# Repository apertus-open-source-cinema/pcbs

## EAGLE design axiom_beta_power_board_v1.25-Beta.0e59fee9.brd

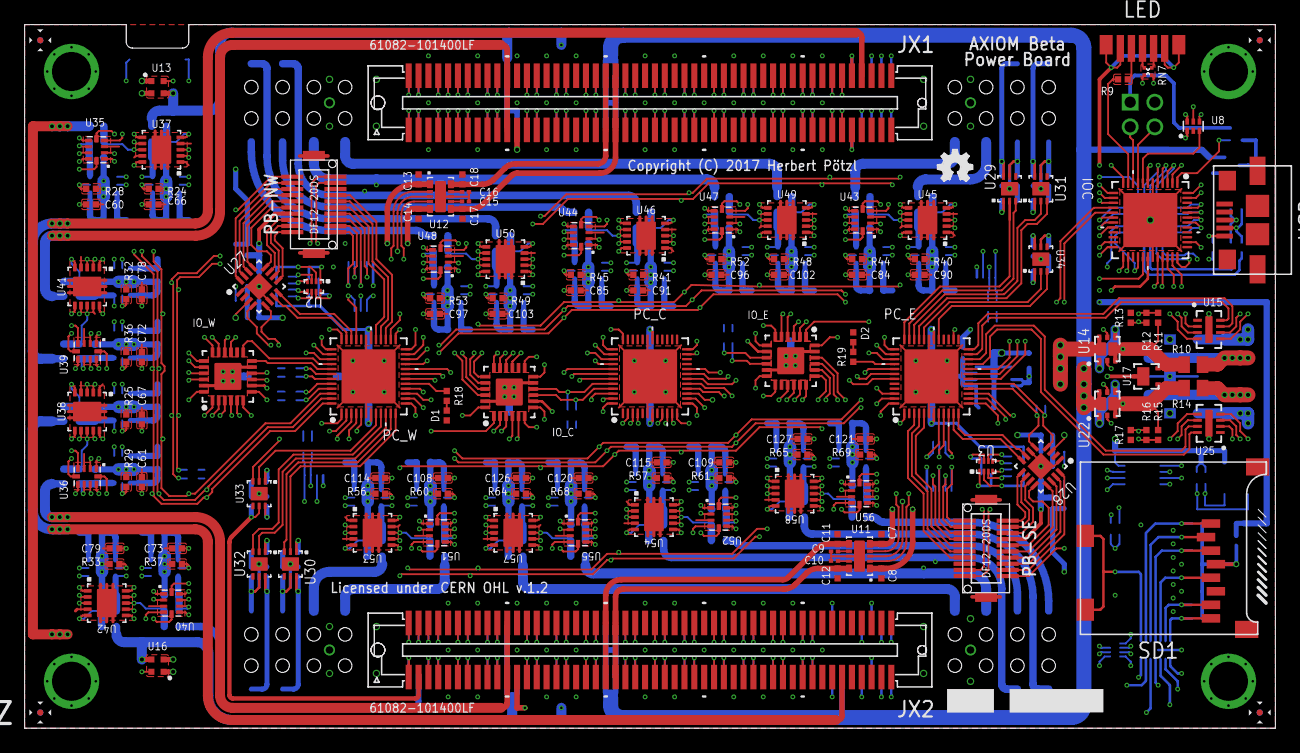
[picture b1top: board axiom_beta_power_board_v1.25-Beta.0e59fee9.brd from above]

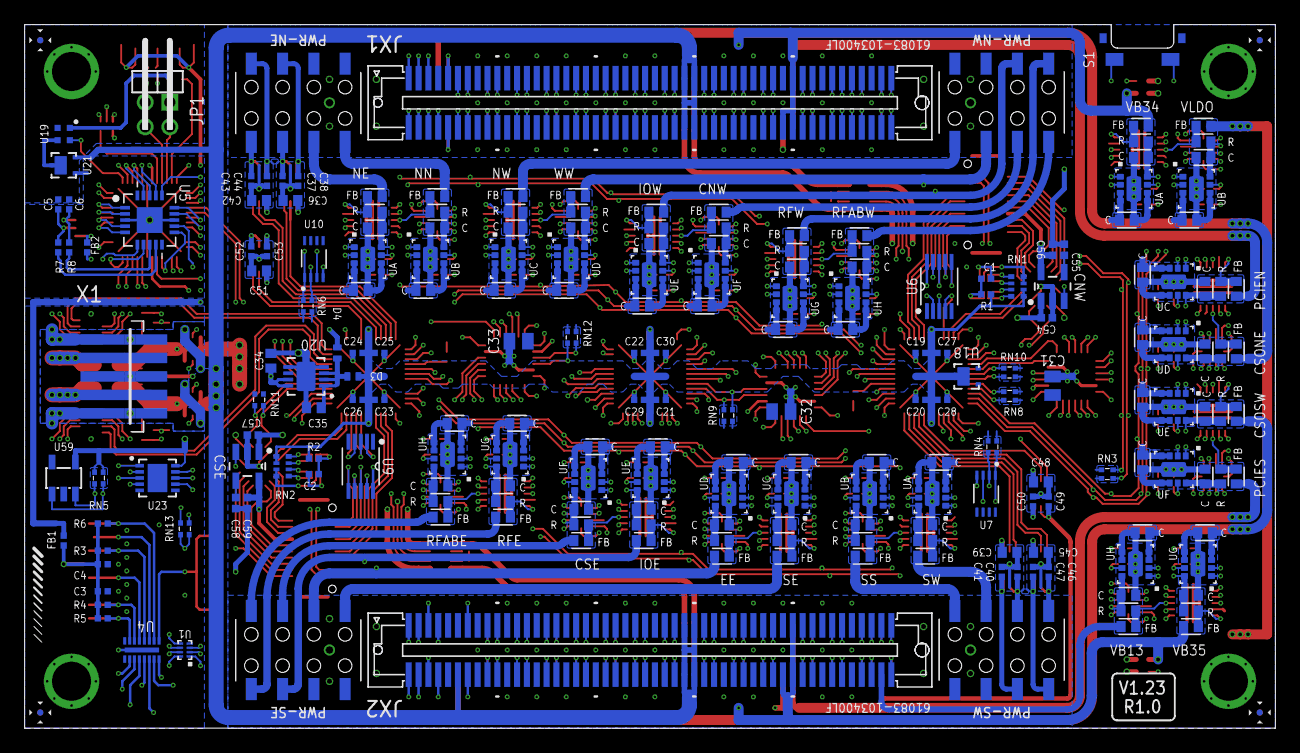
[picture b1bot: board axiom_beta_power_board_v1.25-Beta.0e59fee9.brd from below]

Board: 4 copper layers, 101.6 x 57.1 mm, 354 parts (218 on the bottom side), 496 nets.

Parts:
BETA: µZ-FCI-SOCKET-NOHOLES-R; µZ-SOCKET-NOHOLES-R
C1, C2: 10n; 0402-C
C3, C37, C38, C40, C41, C43, C44, C46, C47, C49, C50, C52, C53: 1u; 0402-C
C4, C19, C20, C21, C22, C23, C24: 100n; 0402-C
C5, C6, C7, C8, C11, C12, C13, C14, C17, C18, C60, C61, C66, C67, C72, C73, C78, C79, C84, C85, C90, C91, C96, C97, C102, C103, C108, C109, C114, C115, C120, C121, C126, C127: 0402-C
C9, C10, C15, C16: 0201-C
C25, C26, C27, C28, C29, C30: 4u7; 0402-C
C31, C32, C33: 47u; 0805-C
C34, C35: 10u; 0603-C
C36, C39, C42, C45, C48, C51: 4u7; 0603-C
C54, C56, C57, C59: 1u; 0402-B
C55, C58: 10n; 0402-B
C62, C63, C64, C65, C68, C69, C70, C71, C74, C75, C76, C77, C80, C81, C82, C83, C86, C87, C88, C89, C92, C93, C94, C95, C98, C99, C100, C101, C104, C105, C106, C107, C110, C111, C112, C113, C116, C117, C118, C119, C122, C123, C124, C125, C128, C129, C130, C131: 0603-C
CNW: SPX3819M5-L; SOT95P280X145-5N
CSE: SPX3819M5-L; SOT95P280X145-5N
D1, D2: 0402-C
D3, D4: PMEG2010BELD; DFN1006D-2
F1, F2, F3, F4, F5, F6, F7, F8: FIDUCIAL; FID_ARROW
FB1, FB2: 0402-C
FB3, FB4, FB5, FB6, FB7, FB8, FB9, FB10, FB11, FB12, FB13, FB14, FB15, FB16, FB17, FB18, FB19, FB20, FB21, FB22, FB23, FB24, FB25, FB26: 0603-C
IOC: PIC16F15386; UQFN40P600X600X100-49N-NSM
IO_C: MCP23018; QFN50P400X400X80-25N-NSM
IO_E: MCP23018; QFN50P400X400X80-25N-NSM
IO_W: MCP23018; QFN50P400X400X80-25N-NSM
JP1: 2X02M/90-S
LED: MSL0104RGB; MSL0104
LOGO2: OSHW_LOGO_FILLX0100-NT; OSHW_FILLX100_NOTEXT
PB-NW: DF12(XX)-20DP-0.5V
PB-SE: DF12(XX)-20DP-0.5V
PC_C: PIC16F15386; UQFN40P600X600X100-49N-NSM
PC_E: PIC16F15386; UQFN40P600X600X100-49N-NSM
PC_W: PIC16F15386; UQFN40P600X600X100-49N-NSM
PWR-NE: PINRC-2X04; R2X04
PWR-NW: PINRC-2X04; R2X04
PWR-SE: PINRC-2X04; R2X04
PWR-SW: PINRC-2X04; R2X04
R1, R2: 200k; 0402-C
R3, R4, R5, R6: 50k; 0402-C
R7, R8, R9, R11, R12, R13, R15, R16, R17, R18, R19, R24, R25, R28, R29, R32, R33, R36, R37, R40, R41, R44, R45, R48, R49, R52, R53, R56, R57, R60, R61, R64, R65, R68, R69: 0402-C
R10, R14: 0805-C
R22, R23, R26, R27, R30, R31, R34, R35, R38, R39, R42, R43, R46, R47, R50, R51, R54, R55, R58, R59, R62, R63, R66, R67: 0603-C
RN1, RN2: 4X0402ARV341
RN3, RN4, RN5, RN6, RN8, RN9, RN10, RN11, RN12, RN13: EXB24V
RN7: EXB14V
S1: SKSNLAE010
SD1: MICRO-SD-2CD; TF-MICRO-SD_PP2
U1: TXS0102; X2SON-8
U2, U3: PCA9306; UDFN-8
U4: IP4251CZ16-8-TTL; SON40P135X330X55-17N
U5: FT231; QFN65P400X400X100-21N
U6, U9: MCP4728-E/UN; SOP50P490X110-10N
U7, U10: LM75BGD; SOT996-2/3
U8: FXLH1T45; MICROPAK-6
U11, U12: AP22966; V-DFN3020-14
U13, U16, U19: MIC94040; MLF-4
U14, U22: NTLUD4C26N; UDFN6
U15, U25: LTC4365; DFN8
U17, U18, U21: PMEG2020CPAS; DFN2020D-3
U20: LT1965; DFN3X3_8LEAD
U23: PAC1720; DFN3X3_10LEAD
U27, U28: MCP23009; QFN50P300X300X80-17N
U29, U30, U31, U32, U33, U34: AP7312-3333W6-7; DFN2018-6
U35, U36, U39, U40, U43, U44, U47, U48, U51, U52, U55, U56: ADS1018; X2QFN-10
U37, U38, U41, U42, U45, U46, U49, U50, U53, U54, U57, U58: MCP46X2; DFN-10
U59: 24AA00OT; SOT23-5L
UA: TPS82085; MICROSIP
UB: TPS82085DD; MICROSIP-DD
UC: TPS82085; MICROSIP
UD: TPS82085DD; MICROSIP-DD
UE: TPS82085; MICROSIP
UF: TPS82085DD; MICROSIP-DD
UG: TPS82085; MICROSIP
UH: TPS82085DD; MICROSIP-DD
USB: 5_USB_3S; MICRO-AB-H-SMT
U_I: TPS82085; MICROSIP
U_J: TPS82085DD; MICROSIP-DD
U_K: TPS82085; MICROSIP
U_L: TPS82085DD; MICROSIP-DD
U_M: TPS82085; MICROSIP
U_N: TPS82085DD; MICROSIP-DD
U_O: TPS82085; MICROSIP
U_P: TPS82085DD; MICROSIP-DD
U_Q: TPS82085; MICROSIP
U_R: TPS82085DD; MICROSIP-DD
U_S: TPS82085; MICROSIP
U_T: TPS82085DD; MICROSIP-DD
U_U: TPS82085; MICROSIP
U_V: TPS82085DD; MICROSIP-DD
U_W: TPS82085; MICROSIP
U_X: TPS82085DD; MICROSIP-DD
X1: PICO-SPOX-5
ZED: µZ-FCI-CONONLY; µZ-CONONLY

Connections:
!ALERT: PC_E.46, U23.7
!CS0: PC_W.36, U35.2
!CS1: PC_W.37, U39.2
!CS2: PC_W.39, U36.2
!CS3: PC_W.38, U40.2
!CS4: PC_C.36, U43.2
!CS5: PC_C.37, U47.2
!CS6: PC_C.38, U44.2
!CS7: PC_C.39, U48.2
!CS8: PC_C.12, U51.2
!CS9: PC_C.13, U55.2
!CS10: PC_C.14, U52.2
!CS11: PC_C.15, U56.2
!RESET: IOC.28, U5.11
ANY_IN: C34.1, U17.3, U17.4, U20.7, U20.8
A_!RST: PB-NW.1, PC_W.25
A_SCL: PB-NW.2, RN1.1, U2.3
A_SDA: PB-NW.4, RN1.2, U2.4
BANK13_00_N: BETA.89, ZED.89
BANK13_00_P: BETA.87, ZED.87
BANK13_01_N: BETA.90, ZED.90
BANK13_01_P: BETA.88, ZED.88
BANK13_02_N: BETA.93, ZED.93
BANK13_02_P: BETA.91, ZED.91
BANK13_03_N: BETA.94, ZED.94
BANK13_03_P: BETA.92, ZED.92
BANK13_04_N: BETA.195, ZED.195
BANK13_04_P: BETA.193, ZED.193
BANK13_05_N: BETA.196, ZED.196
BANK13_05_P: BETA.194, ZED.194
BANK13_06_N: BETA.199, ZED.199
BANK13_06_P: BETA.197, ZED.197
BANK13_SE_0: BETA.200, ZED.200
BETA_5V: C7.1, C8.1, C13.1, C14.1, C31.1, C32.1, C33.1, C60.1, C61.1, C62.1, C64.1, C66.1, C67.1, C68.1, C70.1, C72.1, C73.1, C74.1, C76.1, C78.1, C79.1, C80.1, C82.1, C84.1, C85.1, C86.1, C88.1, C90.1, C91.1, C92.1, C94.1, C96.1, C97.1, C98.1, C100.1, C102.1, C103.1, C104.1, C106.1, C108.1, C109.1, C110.1, C112.1, C114.1, C115.1, C116.1, C118.1, C120.1, C121.1, C122.1, C124.1, C126.1, C127.1, C128.1, C130.1, IO_C.8, IO_E.8, IO_W.8, RN3.3, RN3.4, RN4.3, RN4.4, RN5.3, RN5.4, RN6.3, RN6.4, RN8.3, RN8.4, RN9.3, RN9.4, RN10.3, RN10.4, RN11.3, RN11.4, RN12.3, RN12.4, U6.1, U7.5, U7.6, U7.7, U7.8, U9.1, U10.5, U10.6, U10.7, U10.8, U11.1, U11.3, U11.5, U12.1, U12.3, U12.5, U14.6, U14.D1, U15.6, U18.1, U18.2, U23.10, U27.3, U28.3, U35.8, U36.8, U37.10, U38.9, U38.10, U39.8, U40.8, U41.1, U41.10, U42.1, U42.9, U42.10, U43.8, U44.8, U45.10, U46.9, U46.10, U47.8, U48.8, U49.1, U49.10, U50.1, U50.9, U50.10, U51.8, U52.8, U53.10, U54.9, U54.10, U55.8, U56.8, U57.1, U57.10, U58.1, U58.9, U58.10, U59.4, UA.3, UA.4, UB.3, UB.4, UC.3, UC.4, UD.3, UD.4, UE.3, UE.4, UF.3, UF.4, UG.3, UG.4, UH.3, UH.4, U_I.3, U_I.4, U_J.3, U_J.4, U_K.3, U_K.4, U_L.3, U_L.4, U_M.3, U_M.4, U_N.3, U_N.4, U_O.3, U_O.4, U_P.3, U_P.4, U_Q.3, U_Q.4, U_R.3, U_R.4, U_S.3, U_S.4, U_T.3, U_T.4, U_U.3, U_U.4, U_V.3, U_V.4, U_W.3, U_W.4, U_X.3, U_X.4
BETA_!FAULT: PC_E.24, U15.7
BETA_!SHDN: PC_E.23, U15.8
BETA_GATE: U14.2, U14.5, U15.5
BETA_IN: R10.2, R11.1, U14.3, U14.D2, U15.4, U17.2, U23.2
BETA_OV: R12.2, R13.1, U15.2
BETA_SUP: R10.1, U23.1, X1.4, X1.4A
BETA_UV: R11.2, R12.1, U15.3
BTN: PC_W.26, S1.2
B_!RST: PB-SE.1, PC_E.13
B_SCL: PB-SE.2, RN2.1, U3.3
B_SDA: PB-SE.4, RN2.2, U3.4
CBUS2: IOC.36, U5.7
CC_!MCLR: IOC.20, U5.16
CC_JX1: IOC.8, U8.3
CC_PCLK: IOC.18, U5.15
CC_PDAT: IOC.19, U5.14
CC_SE_0: IOC.47, U1.6
CC_SE_1: IOC.48, U1.7
CD: SD1.CD1, SD1.CD2, U4.1
CD': IOC.32, U4.16
CLK: SD1.5, U4.5
CMD: R3.2, SD1.3, U4.4
CNW_EN: CNW.3, PC_W.22
CNW_PG: C55.1, CNW.4
CSE_EN: CSE.3, PC_E.15
CSE_PG: C58.1, CSE.4
CSO_NE_V: BETA.7, FB9.2
CSO_NW_V: FB14.2, PWR-NW.6
CSO_SE_V: FB22.2, PWR-SE.6
CSO_SW_V: BETA.112, FB4.2
D0: IOC.5, U5.17
D1: IOC.45, U5.1
D2: IOC.3, U5.19
D3: IOC.2, U5.6
D4: IOC.4, U5.18
D5: IOC.43, U5.4
D6: IOC.42, U5.5
D7: IOC.44, U5.2
DAT0: R4.2, SD1.7, U4.6
DAT1: R5.2, SD1.8, U4.7
DAT2: R6.2, SD1.1, U4.2
DAT3: SD1.2, U4.3
DM: R7.2, U5.9
DP: R8.2, U5.8
DXP_0_N: BETA.100, ZED.100
DXP_0_P: BETA.98, ZED.98
EN_A: IO_W.16, UA.1
EN_B: IO_W.18, UB.1
EN_C: IO_W.20, UC.1
EN_D: IO_W.22, UD.1
EN_E: IO_W.1, UE.1
EN_F: IO_W.3, UF.1
EN_G: IO_W.5, UG.1
EN_H: IO_W.7, UH.1
EN_I: IO_E.1, U_I.1
EN_J: IO_E.3, U_J.1
EN_K: IO_E.5, U_K.1
EN_L: IO_E.7, U_L.1
EN_M: IO_C.16, U_M.1
EN_N: IO_C.18, U_N.1
EN_O: IO_C.20, U_O.1
EN_P: IO_C.22, U_P.1
EN_Q: IO_C.1, U_Q.1
EN_R: IO_C.3, U_R.1
EN_S: IO_C.5, U_S.1
EN_T: IO_C.7, U_T.1
EN_U: IO_E.16, U_U.1
EN_V: IO_E.18, U_V.1
EN_W: IO_E.20, U_W.1
EN_X: IO_E.22, U_X.1
EXTA: IOC.10, JP1.2
EXTB: IOC.9, JP1.4
E_B_SCL: PC_E.47, RN2.4, U3.6
E_B_SDA: PC_E.48, RN2.3, U3.5
E_I2C_EN: PC_E.36, U29.2
E_I2C_V: C38.1, PWR-NE.6, U29.6
E_RC2: PC_E.40, R19.1
E_SPI_EN: PC_E.34, U31.2
E_SPI_V: C44.1, PWR-NE.8, U31.6
E_VE: FB25.2, PC_E.1, PWR-SE.4
E_VE_CV: PB-SE.20, U9.6
E_VE_OV: PB-SE.9, U28.13
E_VE_UV: PB-SE.11, U28.12
FAN_SUP: JP1.1, U19.1
FAN_SUP_EN: IOC.1, U19.4
FB_A: R24.2, U37.6, UA.7
FB_B: R28.2, U37.7, UB.7
FB_C: R32.2, U41.6, UC.7
FB_D: R36.2, U41.7, UD.7
FB_E: R25.2, U38.6, UE.7
FB_F: R29.2, U38.7, UF.7
FB_G: R33.2, U42.6, UG.7
FB_H: R37.2, U42.7, UH.7
FB_I: R40.2, U45.6, U_I.7
FB_J: R44.2, U45.7, U_J.7
FB_K: R48.2, U49.6, U_K.7
FB_L: R52.2, U49.7, U_L.7
FB_M: R41.2, U46.6, U_M.7
FB_N: R45.2, U46.7, U_N.7
FB_O: R49.2, U50.6, U_O.7
FB_P: R53.2, U50.7, U_P.7
FB_Q: R56.2, U53.6, U_Q.7
FB_R: R60.2, U53.7, U_R.7
FB_S: R64.2, U57.6, U_S.7
FB_T: R68.2, U57.7, U_T.7
FB_U: R57.2, U54.6, U_U.7
FB_V: R61.2, U54.7, U_V.7
FB_W: R65.2, U58.6, U_W.7
FB_X: R69.2, U58.7, U_X.7
GND: BETA.15, BETA.16, BETA.21, BETA.22, BETA.27, BETA.28, BETA.33, BETA.34, BETA.39, BETA.40, BETA.45, BETA.46, BETA.51, BETA.52, BETA.65, BETA.66, BETA.71, BETA.72, BETA.77, BETA.85, BETA.86, BETA.95, BETA.96, BETA.115, BETA.116, BETA.121, BETA.122, BETA.127, BETA.128, BETA.133, BETA.134, BETA.139, BETA.140, BETA.145, BETA.146, BETA.151, BETA.152, BETA.165, BETA.166, BETA.171, BETA.172, BETA.177, BETA.185, BETA.186, BETA.191, BETA.192, C1.2, C2.2, C3.2, C4.2, C5.2, C6.2, C7.2, C8.2, C9.2, C10.2, C11.2, C12.2, C13.2, C14.2, C15.2, C16.2, C17.2, C18.2, C19.2, C20.2, C21.2, C22.2, C23.2, C24.2, C25.2, C26.2, C27.2, C28.2, C29.2, C30.2, C31.2, C32.2, C33.2, C34.2, C35.2, C36.2, C37.2, C38.2, C39.2, C40.2, C41.2, C42.2, C43.2, C44.2, C45.2, C46.2, C47.2, C48.2, C49.2, C50.2, C51.2, C52.2, C53.2, C54.2, C55.2, C56.2, C57.2, C58.2, C59.2, C60.2, C61.2, C62.2, C63.2, C64.2, C65.2, C66.2, C67.2, C68.2, C69.2, C70.2, C71.2, C72.2, C73.2, C74.2, C75.2, C76.2, C77.2, C78.2, C79.2, C80.2, C81.2, C82.2, C83.2, C84.2, C85.2, C86.2, C87.2, C88.2, C89.2, C90.2, C91.2, C92.2, C93.2, C94.2, C95.2, C96.2, C97.2, C98.2, C99.2, C100.2, C101.2, C102.2, C103.2, C104.2, C105.2, C106.2, C107.2, C108.2, C109.2, C110.2, C111.2, C112.2, C113.2, C114.2, C115.2, C116.2, C117.2, C118.2, C119.2, C120.2, C121.2, C122.2, C123.2, C124.2, C125.2, C126.2, C127.2, C128.2, C129.2, C130.2, C131.2, CNW.2, CSE.2, D1.2, D2.2, IOC.6, IOC.31, IOC.EP, IO_C.11, IO_C.23, IO_C.25, IO_E.11, IO_E.23, IO_E.25, IO_W.11, IO_W.23, IO_W.25, JP1.3, PB-NW.6, PB-SE.6, PC_C.6, PC_C.31, PC_C.EP, PC_E.6, PC_E.31, PC_E.EP, PC_W.6, PC_W.31, PC_W.EP, PWR-NE.2, PWR-NE.4, PWR-NW.1, PWR-NW.3, PWR-SE.1, PWR-SE.3, PWR-SW.2, PWR-SW.4, R13.2, R17.2, R24.1, R25.1, R28.1, R29.1, R32.1, R33.1, R36.1, R37.1, R40.1, R41.1, R44.1, R45.1, R48.1, R49.1, R52.1, R53.1, R56.1, R57.1, R60.1, R61.1, R64.1, R65.1, R68.1, R69.1, S1.1, SD1.6, SD1.MT1, SD1.MT2, U1.4, U2.1, U3.1, U4.17, U5.3, U5.13, U5.EP, U6.10, U7.4, U8.2, U9.10, U10.4, U11.8, U11.EP, U12.8, U12.EP, U13.2, U15.1, U15.EP, U16.2, U19.2, U20.4, U20.5, U20.9, U23.5, U23.6, U23.EPAD, U25.1, U25.EP, U27.1, U27.6, U27.EP, U28.1, U28.6, U28.EP, U29.4, U29.10, U30.4, U30.10, U31.4, U31.10, U32.4, U32.10, U33.4, U33.10, U34.4, U34.10, U35.3, U36.3, U37.1, U37.4, U37.9, U37.EP, U38.1, U38.4, U38.EP, U39.3, U40.3, U41.4, U41.9, U41.EP, U42.4, U42.EP, U43.3, U44.3, U45.1, U45.4, U45.9, U45.EP, U46.1, U46.4, U46.EP, U47.3, U48.3, U49.4, U49.9, U49.EP, U50.4, U50.EP, U51.3, U52.3, U53.1, U53.4, U53.9, U53.EP, U54.1, U54.4, U54.EP, U55.3, U56.3, U57.4, U57.9, U57.EP, U58.4, U58.EP, U59.2, UA.5, UA.6, UA.EP, UB.5, UB.6, UB.EP, UC.5, UC.6, UC.EP, UD.5, UD.6, UD.EP, UE.5, UE.6, UE.EP, UF.5, UF.6, UF.EP, UG.5, UG.6, UG.EP, UH.5, UH.6, UH.EP, USB.5, U_I.5, U_I.6, U_I.EP, U_J.5, U_J.6, U_J.EP, U_K.5, U_K.6, U_K.EP, U_L.5, U_L.6, U_L.EP, U_M.5, U_M.6, U_M.EP, U_N.5, U_N.6, U_N.EP, U_O.5, U_O.6, U_O.EP, U_P.5, U_P.6, U_P.EP, U_Q.5, U_Q.6, U_Q.EP, U_R.5, U_R.6, U_R.EP, U_S.5, U_S.6, U_S.EP, U_T.5, U_T.6, U_T.EP, U_U.5, U_U.6, U_U.EP, U_V.5, U_V.6, U_V.EP, U_W.5, U_W.6, U_W.EP, U_X.5, U_X.6, U_X.EP, X1.1, X1.1A, X1.5, X1.5A, ZED.15, ZED.16, ZED.21, ZED.22, ZED.27, ZED.28, ZED.33, ZED.34, ZED.39, ZED.40, ZED.45, ZED.46, ZED.51, ZED.52, ZED.65, ZED.66, ZED.71, ZED.72, ZED.77, ZED.85, ZED.86, ZED.95, ZED.96, ZED.115, ZED.116, ZED.121, ZED.122, ZED.127, ZED.128, ZED.133, ZED.134, ZED.139, ZED.140, ZED.145, ZED.146, ZED.151, ZED.152, ZED.165, ZED.166, ZED.171, ZED.172, ZED.177, ZED.185, ZED.186, ZED.191, ZED.192
IOC_!RST: IO_C.12, PC_C.46
IOC_INT: IO_C.13, PC_C.40
IOC_SCL: IO_C.9, PC_C.45, RN9.2
IOC_SDA: IO_C.10, PC_C.44, RN9.1
IOE_!RST: IO_E.12, PC_C.23
IOE_INT: IO_E.13, PC_C.24
IOE_SCL: IO_E.9, RN12.2
IOE_SDA: IO_E.10, RN12.1
IOE_V: FB20.2, PWR-SE.5, RN2.7, RN2.8, U3.2
IONW_SCL: PC_W.43, RN10.2, U27.4
IONW_SDA: PC_W.42, RN10.1, U27.5
IOSE_SCL: PC_E.17, RN11.1, U28.4
IOSE_SDA: PC_E.16, RN11.2, U28.5
IOW_!RST: IO_W.12, PC_W.41
IOW_INT: IO_W.13, PC_W.40
IOW_SCL: IO_W.9, PC_W.45, RN8.2
IOW_SDA: IO_W.10, PC_W.44, RN8.1
IOW_V: FB12.2, PWR-NW.5, RN1.7, RN1.8, U2.2
JTAG_EN: PC_W.10, U32.2
JTAG_V: C47.1, PWR-SW.8, U32.6
JX1_00_N: BETA.13, ZED.13
JX1_00_P: BETA.11, ZED.11
JX1_01_N: BETA.14, ZED.14
JX1_01_P: BETA.12, ZED.12
JX1_02_N: BETA.19, ZED.19
JX1_02_P: BETA.17, ZED.17
JX1_03_N: BETA.20, ZED.20
JX1_03_P: BETA.18, ZED.18
JX1_04_N: BETA.25, ZED.25
JX1_04_P: BETA.23, ZED.23
JX1_05_N: BETA.26, ZED.26
JX1_05_P: BETA.24, ZED.24
JX1_06_N: BETA.31, ZED.31
JX1_06_P: BETA.29, ZED.29
JX1_07_N: BETA.32, ZED.32
JX1_07_P: BETA.30, ZED.30
JX1_08_N: BETA.37, ZED.37
JX1_08_P: BETA.35, ZED.35
JX1_09_N: BETA.38, ZED.38
JX1_09_P: BETA.36, ZED.36
JX1_10_N: BETA.43, ZED.43
JX1_10_P: BETA.41, ZED.41
JX1_11_N: BETA.44, ZED.44
JX1_11_P: BETA.42, ZED.42
JX1_12_N: BETA.49, ZED.49
JX1_12_P: BETA.47, ZED.47
JX1_13_N: BETA.50, ZED.50
JX1_13_P: BETA.48, ZED.48
JX1_14_N: BETA.55, ZED.55
JX1_14_P: BETA.53, ZED.53
JX1_15_N: BETA.56, ZED.56
JX1_15_P: BETA.54, ZED.54
JX1_16_N: BETA.63, ZED.63
JX1_16_P: BETA.61, ZED.61
JX1_17_N: BETA.64, ZED.64
JX1_17_P: BETA.62, ZED.62
JX1_18_N: BETA.69, ZED.69
JX1_18_P: BETA.67, ZED.67
JX1_19_N: BETA.70, ZED.70
JX1_19_P: BETA.68, ZED.68
JX1_20_N: BETA.75, ZED.75
JX1_20_P: BETA.73, ZED.73
JX1_21_N: BETA.76, ZED.76
JX1_21_P: BETA.74, ZED.74
JX1_22_N: BETA.83, ZED.83
JX1_22_P: BETA.81, ZED.81
JX1_23_N: BETA.84, ZED.84
JX1_23_P: BETA.82, ZED.82
JX1_DIR: IOC.38, U8.5
JX1_SE_0: BETA.9, ZED.9
JX1_SE_1: BETA.10, U8.4, ZED.10
JX2_00_N: BETA.119, ZED.119
JX2_00_P: BETA.117, ZED.117
JX2_01_N: BETA.120, ZED.120
JX2_01_P: BETA.118, ZED.118
JX2_02_N: BETA.125, ZED.125
JX2_02_P: BETA.123, ZED.123
JX2_03_N: BETA.126, ZED.126
JX2_03_P: BETA.124, ZED.124
JX2_04_N: BETA.131, ZED.131
JX2_04_P: BETA.129, ZED.129
JX2_05_N: BETA.132, ZED.132
JX2_05_P: BETA.130, ZED.130
JX2_06_N: BETA.137, ZED.137
JX2_06_P: BETA.135, ZED.135
JX2_07_N: BETA.138, ZED.138
JX2_07_P: BETA.136, ZED.136
JX2_08_N: BETA.143, ZED.143
JX2_08_P: BETA.141, ZED.141
JX2_09_N: BETA.144, ZED.144
JX2_09_P: BETA.142, ZED.142
JX2_10_N: BETA.149, ZED.149
JX2_10_P: BETA.147, ZED.147
JX2_11_N: BETA.150, ZED.150
JX2_11_P: BETA.148, ZED.148
JX2_12_N: BETA.155, ZED.155
JX2_12_P: BETA.153, ZED.153
JX2_13_N: BETA.156, ZED.156
JX2_13_P: BETA.154, ZED.154
JX2_14_N: BETA.163, ZED.163
JX2_14_P: BETA.161, ZED.161
JX2_15_N: BETA.164, ZED.164
JX2_15_P: BETA.162, ZED.162
JX2_16_N: BETA.169, ZED.169
JX2_16_P: BETA.167, ZED.167
JX2_17_N: BETA.170, ZED.170
JX2_17_P: BETA.168, ZED.168
JX2_18_N: BETA.175, ZED.175
JX2_18_P: BETA.173, ZED.173
JX2_19_N: BETA.176, ZED.176
JX2_19_P: BETA.174, ZED.174
JX2_20_N: BETA.183, ZED.183
JX2_20_P: BETA.181, ZED.181
JX2_21_N: BETA.184, ZED.184
JX2_21_P: BETA.182, ZED.182
JX2_22_N: BETA.189, ZED.189
JX2_22_P: BETA.187, ZED.187
JX2_23_N: BETA.190, ZED.190
JX2_23_P: BETA.188, ZED.188
JX2_SE_0: U1.3, ZED.113
JX2_SE_1: U1.2, ZED.114
LED_B: IOC.25, RN7.2
LED_G: IOC.11, R9.2
LED_R: IOC.26, RN7.1
MEAS_A: FB3.1, R22.2, U35.4, U37.5
MEAS_B: FB5.1, R26.2, U35.6, U37.8
MEAS_C: FB7.1, R30.2, U39.4, U41.5
MEAS_D: FB9.1, R34.2, U39.6, U41.8
MEAS_E: FB4.1, R23.2, U36.4, U38.5
MEAS_F: FB6.1, R27.2, U36.6, U38.8
MEAS_G: FB8.1, R31.2, U40.4, U42.5
MEAS_H: FB10.1, R35.2, U40.6, U42.8
MEAS_I: FB11.1, R38.2, U43.4, U45.5
MEAS_J: FB13.1, R42.2, U43.6, U45.8
MEAS_K: FB15.1, R46.2, U47.4, U49.5
MEAS_L: FB17.1, R50.2, U47.6, U49.8
MEAS_M: FB12.1, R39.2, U44.4, U46.5
MEAS_N: FB14.1, R43.2, U44.6, U46.8
MEAS_O: FB16.1, R47.2, U48.4, U50.5
MEAS_P: FB18.1, R51.2, U48.6, U50.8
MEAS_Q: FB19.1, R54.2, U51.4, U53.5
MEAS_R: FB21.1, R58.2, U51.6, U53.8
MEAS_S: FB23.1, R62.2, U55.4, U57.5
MEAS_T: FB25.1, R66.2, U55.6, U57.8
MEAS_U: FB20.1, R55.2, U52.4, U54.5
MEAS_V: FB22.1, R59.2, U52.6, U54.8
MEAS_W: FB24.1, R63.2, U56.4, U58.5
MEAS_X: FB26.1, R67.2, U56.6, U58.8
MIX_SUP: U19.3, U21.3, U21.4
unnamed: C3.1, C4.1, FB1.2, R3.1, R4.1, R5.1, R6.1, SD1.4
unnamed: LED.5, RN7.3
unnamed: LED.4, RN7.4
unnamed: LED.3, R9.1
unnamed: C5.1, R7.1, USB.2
unnamed: C6.1, R8.1, USB.3
unnamed: U14.1, U14.4
unnamed: C15.1, U12.7
unnamed: C16.1, U12.9
unnamed: C9.1, U11.7
unnamed: C10.1, U11.9
unnamed: D1.1, R18.2
unnamed: D2.1, R19.2
unnamed: C1.1, R1.2, U2.7, U2.8
unnamed: C2.1, R2.2, U3.7, U3.8
unnamed: U22.1, U22.4
NW_!LDAC: PC_W.33, U6.4
NW_!RST: PC_W.35, U27.7
NW_INT: PC_W.34, U27.8
N_CHK_V: C56.1, CNW.5, PB-NW.13, PC_W.23
N_I2C_EN: PC_E.33, U31.3
N_I2C_V: C43.1, PWR-NE.7, U31.5
N_SPI_EN: PC_E.35, U29.3
N_SPI_V: C37.1, PWR-NE.5, U29.5
N_VE: FB11.2, PWR-NE.3
N_VE_CV: PB-NW.18, U6.7
N_VE_OV: PB-NW.7, U27.14
N_VE_RS: PB-NW.8, PC_W.27
N_VE_UV: PB-NW.19, U27.9
N_VN: FB13.2, PWR-NE.1
N_VN_CV: PB-NW.16, U6.8
N_VN_OV: PB-NW.5, U27.15
N_VN_RS: PB-NW.12, PC_W.29
N_VN_UV: PB-NW.17, U27.10
N_VW: FB15.2, PWR-NW.2
N_VW_CV: PB-NW.14, U6.9
N_VW_OV: PB-NW.3, U27.16
N_VW_RS: PB-NW.10, PC_W.28
N_VW_UV: PB-NW.15, U27.11
OS2: PC_E.26, U10.3
OS3: PC_W.13, U7.3
PCC_!MCLR: PC_C.20, PC_E.41
PCC_PCLK: PC_C.18, PC_E.43
PCC_PDAT: PC_C.19, PC_E.42
PCE_!MCLR: IOC.29, PC_E.20
PCE_PCLK: IOC.17, PC_E.18
PCE_PDAT: IOC.16, PC_E.19
PCIE_I2C_EN: PC_W.1, U33.3
PCIE_I2C_V: BETA.198, C49.1, U33.5
PCIE_NIO_EN: PC_W.21, U13.4
PCIE_N_5V: BETA.59, BETA.60, C18.1, U12.10
PCIE_N_V: BETA.79, BETA.80, FB7.2
PCIE_N_VCCIO: BETA.78, U13.1
PCIE_SIO_EN: PC_W.14, U16.4
PCIE_S_5V: BETA.159, BETA.160, C11.1, U11.6
PCIE_S_V: BETA.179, BETA.180, FB6.2
PCIE_S_VCCIO: BETA.178, U16.1
PCW_!MCLR: PC_C.41, PC_W.20
PCW_PCLK: PC_C.43, PC_W.18
PCW_PDAT: PC_C.42, PC_W.19
PEX_N_V: BETA.57, BETA.58, C17.1, U12.6
PEX_S_V: BETA.157, BETA.158, C12.1, U11.10
PG_A: IO_W.15, UA.2
PG_B: IO_W.17, UB.2
PG_C: IO_W.19, UC.2
PG_D: IO_W.21, UD.2
PG_E: IO_W.24, UE.2
PG_F: IO_W.2, UF.2
PG_G: IO_W.4, UG.2
PG_H: IO_W.6, UH.2
PG_I: IO_E.24, U_I.2
PG_J: IO_E.2, U_J.2
PG_K: IO_E.4, U_K.2
PG_L: IO_E.6, U_L.2
PG_M: IO_C.15, U_M.2
PG_N: IO_C.17, U_N.2
PG_O: IO_C.19, U_O.2
PG_P: IO_C.21, U_P.2
PG_Q: IO_C.24, U_Q.2
PG_R: IO_C.2, U_R.2
PG_S: IO_C.4, U_S.2
PG_T: IO_C.6, U_T.2
PG_U: IO_E.15, U_U.2
PG_V: IO_E.17, U_V.2
PG_W: IO_E.19, U_W.2
PG_X: IO_E.21, U_X.2
PMOD_D0: U4.10, ZED.101
PMOD_D1: U4.11, ZED.102
PMOD_D2: U4.13, ZED.103
PMOD_D3: U4.12, ZED.104
PMOD_D6: U4.15, ZED.107
PMOD_D7: U4.14, ZED.108
PMOD_SCL: IOC.34, RN13.2, ZED.105
PMOD_SDA: IOC.35, RN13.1, ZED.106
RFAB_E_V: FB26.2, PWR-SE.8
RFAB_W_V: FB18.2, PWR-NW.8
RFE_V: FB24.2, PWR-SE.7
RFW_V: FB16.2, PWR-NW.7
SCK1: PC_W.46, U35.1, U36.1, U39.1, U40.1
SCK2: PC_C.9, U43.1, U44.1, U47.1, U48.1
SCK3: PC_C.4, U51.1, U52.1, U55.1, U56.1
SCL1: PC_W.5, RN3.2, U6.2, U37.2, U38.2, U41.2, U42.2
SCL2: PC_C.16, RN6.1, U10.2, U45.2, U46.2, U49.2, U50.2
SCL3: PC_C.48, RN4.1, U7.2, U53.2, U54.2, U57.2, U58.2
SCL4: PC_E.8, RN5.2, U9.2, U23.9, U59.1
SDA1: PC_W.4, RN3.1, U6.3, U37.3, U38.3, U41.3, U42.3
SDA2: PC_C.17, RN6.2, U10.1, U45.3, U46.3, U49.3, U50.3
SDA3: PC_C.47, RN4.2, U7.1, U53.3, U54.3, U57.3, U58.3
SDA4: PC_E.9, RN5.1, U9.3, U23.8, U59.3
SDI1: PC_W.48, U35.10, U36.10, U39.10, U40.10
SDI2: PC_C.10, U43.10, U44.10, U47.10, U48.10
SDI3: PC_C.3, U51.10, U52.10, U55.10, U56.10
SDO1: PC_W.47, U35.9, U36.9, U39.9, U40.9
SDO2: PC_C.11, U43.9, U44.9, U47.9, U48.9
SDO3: PC_C.2, U51.9, U52.9, U55.9, U56.9
SD_V: C52.1, FB1.1, U34.5
SD_V_EN: PC_E.29, U34.3
SENSE: X1.3, X1.3A
SE_!LDAC: PC_E.10, U9.4
SE_!RST: PC_E.12, U28.7
SE_INT: PC_E.11, U28.8
S_CHK_V: C59.1, CSE.5, PB-SE.13, PC_E.14
S_I2C_EN: PC_W.9, U32.3
S_I2C_V: C46.1, PWR-SW.7, U32.5
S_SPI_EN: PC_W.11, U30.3
S_SPI_V: C40.1, PWR-SW.5, U30.5
S_VE: FB23.2, PWR-SE.2
S_VE_CV: PB-SE.14, U9.9
S_VE_OV: PB-SE.3, U28.16
S_VE_RS: PB-SE.10, PC_E.4
S_VE_UV: PB-SE.15, U28.11
S_VS: FB21.2, PWR-SW.1
S_VS_CV: PB-SE.16, U9.8
S_VS_OV: PB-SE.5, U28.15
S_VS_RS: PB-SE.12, PC_E.5
S_VS_UV: PB-SE.17, U28.10
S_VW: FB19.2, PWR-SW.3
S_VW_CV: PB-SE.18, U9.7
S_VW_OV: PB-SE.7, U28.14
S_VW_RS: PB-SE.8, PC_E.3
S_VW_UV: PB-SE.19, U28.9
UNUSED_EN: PC_W.8, U33.2
UNUSED_V: C50.1, U33.6
V33: C35.1, D3.A, D4.A, U20.1, U20.2, U20.3
VBUS: FB2.2, USB.1
VCC: C53.1, D4.C, IOC.7, IOC.30, LED.1, LED.2, LED.6, LED.7, RN13.3, RN13.4, U1.8, U5.20, U8.1, U21.1, U34.6
VCCO_13: FB10.2, ZED.198
VCCO_34: FB3.2, U8.6, U13.3, ZED.78, ZED.79, ZED.80
VCCO_35: FB8.2, U1.1, U1.5, U16.3, ZED.178, ZED.179, ZED.180
VCC_EN: PC_E.32, U34.2
VLDO: C36.1, C39.1, C42.1, C45.1, C48.1, C51.1, C54.1, C57.1, CNW.1, CSE.1, FB5.2, U29.1, U30.1, U31.1, U32.1, U33.1, U34.1
VOUT_A: C63.1, R22.1, U35.5, UA.8
VOUT_B: C69.1, R26.1, U35.7, UB.8
VOUT_C: C75.1, R30.1, U39.5, UC.8
VOUT_D: C81.1, R34.1, U39.7, UD.8
VOUT_E: C65.1, R23.1, U36.5, UE.8
VOUT_F: C71.1, R27.1, U36.7, UF.8
VOUT_G: C77.1, R31.1, U40.5, UG.8
VOUT_H: C83.1, R35.1, U40.7, UH.8
VOUT_I: C87.1, R38.1, U43.5, U_I.8
VOUT_J: C93.1, R42.1, U43.7, U_J.8
VOUT_K: C99.1, R46.1, U47.5, U_K.8
VOUT_L: C105.1, R50.1, U47.7, U_L.8
VOUT_M: C89.1, R39.1, U44.5, U_M.8
VOUT_N: C95.1, R43.1, U44.7, U_N.8
VOUT_O: C101.1, R47.1, U48.5, U_O.8
VOUT_P: C107.1, R51.1, U48.7, U_P.8
VOUT_Q: C111.1, R54.1, U51.5, U_Q.8
VOUT_R: C117.1, R58.1, U51.7, U_R.8
VOUT_S: C123.1, R62.1, U55.5, U_S.8
VOUT_T: C129.1, R66.1, U55.7, U_T.8
VOUT_U: C113.1, R55.1, U52.5, U_U.8
VOUT_V: C119.1, R59.1, U52.7, U_V.8
VOUT_W: C125.1, R63.1, U56.5, U_W.8
VOUT_X: C131.1, R67.1, U56.7, U_X.8
VPC: C19.1, C20.1, C21.1, C22.1, C23.1, C24.1, C25.1, C26.1, C27.1, C28.1, C29.1, C30.1, D3.C, PC_C.7, PC_C.30, PC_E.7, PC_E.30, PC_W.7, PC_W.30, R1.1, R2.1, RN1.5, RN1.6, RN2.5, RN2.6, U18.3, U18.4
VP_0_N: BETA.99, ZED.99
VP_0_P: BETA.97, ZED.97
VUSB: FB2.1, U5.12
W_A_SCL: PC_W.2, RN1.4, U2.6
W_A_SDA: PC_W.3, RN1.3, U2.5
W_I2C_EN: PC_W.12, U30.2
W_I2C_V: C41.1, PWR-SW.6, U30.6
W_RB5: PC_W.17, R18.1
W_VW: FB17.2, PC_W.24, PWR-NW.4
W_VW_CV: PB-NW.20, U6.6
W_VW_OV: PB-NW.9, U27.13
W_VW_UV: PB-NW.11, U27.12
ZED_5V: U21.2, U22.6, U22.D1, U25.6, ZED.57, ZED.58, ZED.59, ZED.60, ZED.112, ZED.157, ZED.158, ZED.159, ZED.160
ZED_!FAULT: PC_E.22, U25.7
ZED_!SHDN: PC_E.21, U25.8
ZED_!SRST: IOC.23, ZED.6
ZED_DONE: IOC.24, ZED.8
ZED_GATE: U22.2, U22.5, U25.5
ZED_IN: R14.2, R15.1, U17.1, U22.3, U22.D2, U23.4, U25.4
ZED_OV: R16.2, R17.1, U25.2
ZED_PWR_EN: IOC.33, ZED.5
ZED_SUP: R14.1, U23.3, X1.2, X1.2A
ZED_TCK: IOC.13, ZED.1
ZED_TDI: IOC.15, ZED.4
ZED_TDO: IOC.12, ZED.3
ZED_TMS: IOC.14, ZED.2
ZED_UV: R15.2, R16.1, U25.3

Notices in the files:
axiom_beta_power_board_v1.25-Beta.0e59fee9.brd:
Copyright (C) 2017 Herbert Pötzl
Licensed under CERN OHL v.1.2
axiom_beta_power_board_v2.23-Beta.45bfb2f5.brd:
Copyright (C) 2017-2018 Herbert Pötzl
axiom_beta_sensor_cmv12000_tht_v0.16-Beta.e3d80774.brd:
Copyright (C) 2015-2017 H.Pötzl
